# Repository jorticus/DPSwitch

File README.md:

# DPSwitch #

*License: CERN-OHL-S v2*

DPSwitch is a simple KVM-style device that allows you to switch Display Port & USB2.0 between two source devices (eg. a Laptop and a PC):

It is built around the HD3SS215 DP/HDMI mux chip by Texas Instruments, and has a simple flip-flop circuit and two physical buttons to select the input to route to the output. No firmware is required!

I abuse the HD3SS215's HDMI DDC lines to switch USB2.0 signals, and while the datasheet doesn't specify a maximum bandwidth for these lines, it appears to work fine. This avoids the need for a separate mux to switch USB.

## Bill of Materials ##

Qty | Description               | Part Number
----|---------------------------|------------
  1 | DP/HDMI 2:1 Mux 6Gbps     | HD3SS215RTQT
  1 | Dual NAND Gate            | 74LVC2G00DC,125
  1 | 0603 Side look LED (Blue) | KPA-1606QBC-D
  2 | 0603 SMD LED (Green)      | 
  2 | Button (SMD)              | PTS645*
  1 | USB Type-A Conn (TH)      | SS-52100-001
  2 | Micro USB Conn (SMD)      | 609-5379-2-ND 
  2 | Diode                     | BAT54GWJ
  3 | DisplayPort Conn          | MOLEX 47272-0001

Plus various 0603 resistors & capacitors. See schematic.

## Manufacturing ##

Since DP operates in the GHz range, the PCB must be impedance controlled, and utilizes a 4 layer stackup. I used JLCPCB's 4-layer '[JLC7628](https://jlcpcb.com/quote/pcbOrderFaq/PCB%20Stackup)' PCB with a dielectric constant of 4.6, and a black solder mask.

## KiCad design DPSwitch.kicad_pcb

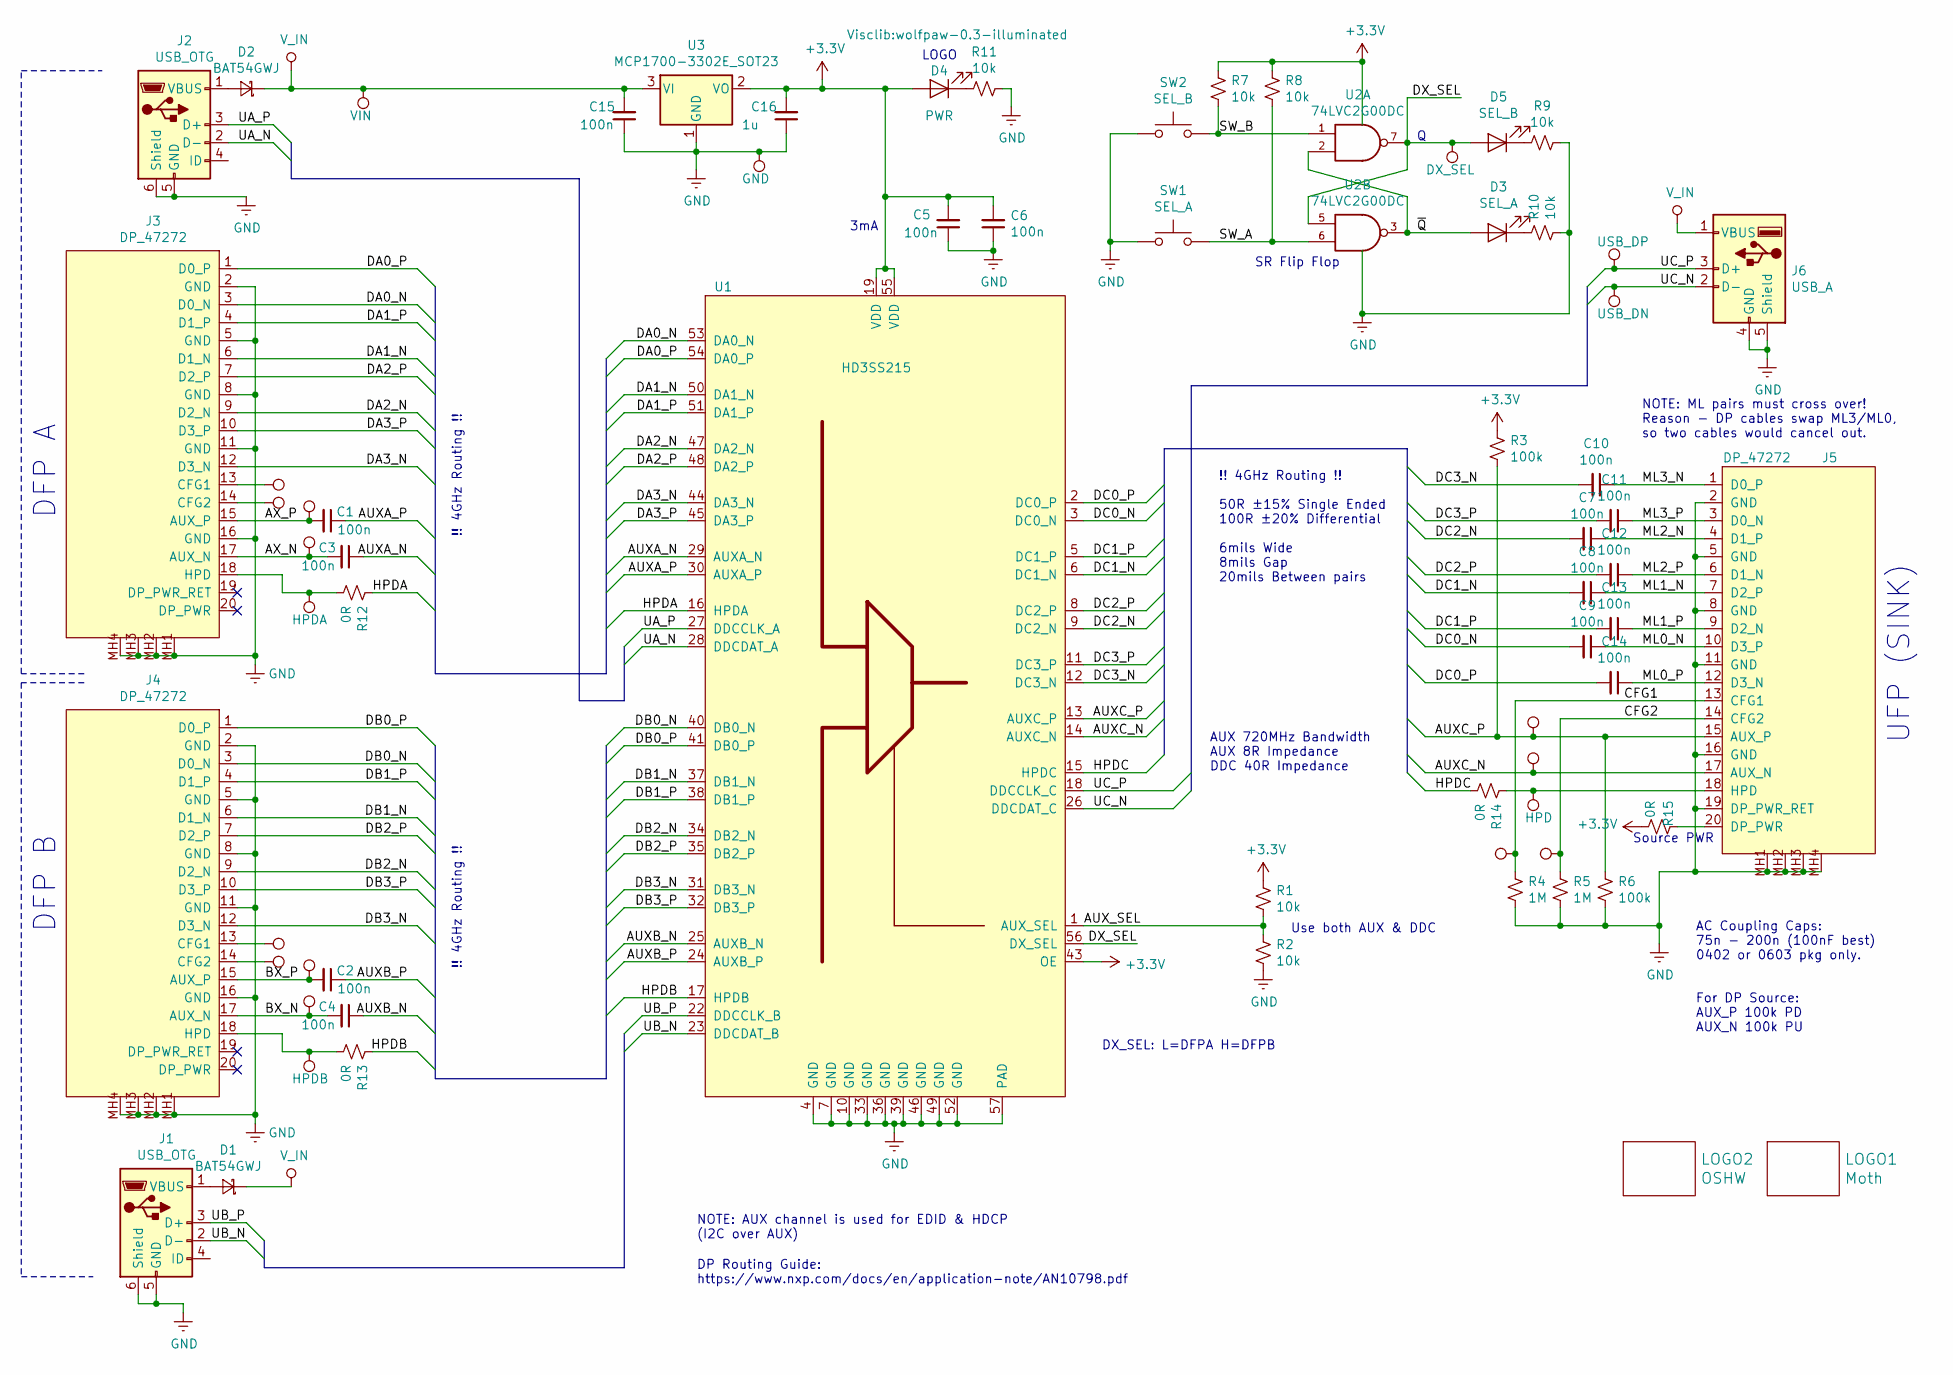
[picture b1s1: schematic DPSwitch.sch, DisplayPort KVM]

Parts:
C1, C2, C3, C4, C5, C6, C7, C8, C9, C10, C11, C12, C13, C14, C15: 100n; C_0603_HandSoldering
C16: 1u; C_0805_HandSoldering
D1, D2: BAT54GWJ; D_SOD-123
D3: SEL_A; LED_0603_HandSoldering
D4: PWR; wolfpaw-0.3-illuminated
D5: SEL_B; LED_0603_HandSoldering
J1, J2: USB_OTG; USB-B-MICRO-SMD
J3, J4, J5: DP_47272; 472720024
J6: USB_A
LOGO1: Moth; moth
LOGO2: OSHW; OSHW-LOGO-M
R1, R2, R7, R8, R9, R10, R11: 10k; R_0603_HandSoldering
R3, R6: 100k; R_0603_HandSoldering
R4, R5: 1M; R_0603_HandSoldering
R12, R13, R14, R15: 0R; R_0603_HandSoldering
SW1: SEL_A; SW_SPST_PTS645
SW2: SEL_B; SW_SPST_PTS645
TP1: CFG1A; TP-1MM
TP2: CFG2A; TP-1MM
TP3: CFG1B; TP-1MM
TP4: CFG2B; TP-1MM
TP5: AUXA_P; TP-1MM
TP6: AUXA_N; TP-1MM
TP7: HPDA; TP-1MM
TP8: AUXB_P; TP-1MM
TP9: AUXB_N; TP-1MM
TP10: HPDB; TP-1MM
TP11: VIN; TP-1MM
TP13: DX_SEL; TP-1MM
TP14: CFG1; TP-1MM
TP15: AUX_P; TP-1MM
TP16: AUX_N; TP-1MM
TP17: HPD; TP-1MM
TP18: CFG2; TP-1MM
TP19: USB_DP; TP-1MM
TP20: USB_DN; TP-1MM
TP21: GND; TP-1MM
U1: HD3SS215; VQFN-56_EP_7.8x7.8_Pitch0.5mm
U2: 74LVC2G00DC; VSSOP-8_2.4x2.1mm_Pitch0.5mm
U3: MCP1700-3302E_SOT23; SOT-23

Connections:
+3V3: C5.2, C6.2, C16.2, D4.2 (A), R1.1, R3.1, R7.1, R8.1, R15.2, U1.19 (VDD), U1.43 (OE), U1.55 (VDD), U2.8 (VCC), U3.2 (VO)
/AUXA_N: C3.1, U1.29 (AUXA_N)
/AUXA_P: C1.1, U1.30 (AUXA_P)
/AUXB_N: C4.1, U1.25 (AUXB_N)
/AUXB_P: C2.1, U1.24 (AUXB_P)
/AUXC_N: J5.17 (AUX_N), TP16.1, U1.14 (AUXC_N)
/AUXC_P: J5.15 (AUX_P), R3.2, R6.1, TP15.1, U1.13 (AUXC_P)
/AUX_SEL: R1.2, R2.1, U1.1 (AUX_SEL)
/AX_N: C3.2, J3.17 (AUX_N), TP6.1
/AX_P: C1.2, J3.15 (AUX_P), TP5.1
/BX_N: C4.2, J4.17 (AUX_N), TP9.1
/BX_P: C2.2, J4.15 (AUX_P), TP8.1
/CFG1: J5.13 (CFG1), R4.1, TP14.1
/CFG2: J5.14 (CFG2), R5.1, TP18.1
/DA0_N: J3.3 (D0_N), U1.53 (DA0_N)
/DA0_P: J3.1 (D0_P), U1.54 (DA0_P)
/DA1_N: J3.6 (D1_N), U1.50 (DA1_N)
/DA1_P: J3.4 (D1_P), U1.51 (DA1_P)
/DA2_N: J3.9 (D2_N), U1.47 (DA2_N)
/DA2_P: J3.7 (D2_P), U1.48 (DA2_P)
/DA3_N: J3.12 (D3_N), U1.44 (DA3_N)
/DA3_P: J3.10 (D3_P), U1.45 (DA3_P)
/DB0_N: J4.3 (D0_N), U1.40 (DB0_N)
/DB0_P: J4.1 (D0_P), U1.41 (DB0_P)
/DB1_N: J4.6 (D1_N), U1.37 (DB1_N)
/DB1_P: J4.4 (D1_P), U1.38 (DB1_P)
/DB2_N: J4.9 (D2_N), U1.34 (DB2_N)
/DB2_P: J4.7 (D2_P), U1.35 (DB2_P)
/DB3_N: J4.12 (D3_N), U1.31 (DB3_N)
/DB3_P: J4.10 (D3_P), U1.32 (DB3_P)
/DC0_N: C9.2, U1.3 (DC0_N)
/DC0_P: C14.2, U1.2 (DC0_P)
/DC1_N: C8.2, U1.6 (DC1_N)
/DC1_P: C13.2, U1.5 (DC1_P)
/DC2_N: C7.2, U1.9 (DC2_N)
/DC2_P: C12.2, U1.8 (DC2_P)
/DC3_N: C10.2, U1.12 (DC3_N)
/DC3_P: C11.2, U1.11 (DC3_P)
/DX_SEL: D5.2 (A), TP13.1, U1.56 (DX_SEL), U2.5, U2.7
/HPDA: R12.1, U1.16 (HPDA)
/HPDB: R13.1, U1.17 (HPDB)
/HPDC: R14.2, U1.15 (HPDC)
/ML0_N: C9.1, J5.10 (D3_P)
/ML0_P: C14.1, J5.12 (D3_N)
/ML1_N: C8.1, J5.7 (D2_P)
/ML1_P: C13.1, J5.9 (D2_N)
/ML2_N: C7.1, J5.4 (D1_P)
/ML2_P: C12.1, J5.6 (D1_N)
/ML3_N: C10.1, J5.1 (D0_P)
/ML3_P: C11.1, J5.3 (D0_N)
/SW_A: R8.2, SW1.2, U2.6
/SW_B: R7.2, SW2.2, U2.1
/UA_N: J2.2 (D-), U1.28 (DDCDAT_A)
/UA_P: J2.3 (D+), U1.27 (DDCCLK_A)
/UB_N: J1.2 (D-), U1.23 (DDCDAT_B)
/UB_P: J1.3 (D+), U1.22 (DDCCLK_B)
/UC_N: J6.2 (D-), TP20.1, U1.26 (DDCDAT_C)
/UC_P: J6.3 (D+), TP19.1, U1.18 (DDCCLK_C)
/~Q: D3.2 (A), U2.2, U2.3
GND: C5.1, C6.1, C15.1, C16.1, J1.5 (GND), J1.6 (Shield), J2.5 (GND), J2.6 (Shield), J3.2 (GND), J3.5 (GND), J3.8 (GND), J3.11 (GND), J3.16 (GND), J3.MH1, J3.MH2, J3.MH3, J3.MH4, J4.2 (GND), J4.5 (GND), J4.8 (GND), J4.11 (GND), J4.16 (GND), J4.MH1, J4.MH2, J4.MH3, J4.MH4, J5.2 (GND), J5.5 (GND), J5.8 (GND), J5.11 (GND), J5.16 (GND), J5.19 (DP_PWR_RET), J5.MH1, J5.MH2, J5.MH3, J5.MH4, J6.4 (GND), J6.5 (Shield), R2.2, R4.2, R5.2, R6.2, R9.1, R10.2, R11.1, SW1.1, SW2.1, TP21.1, U1.4 (GND), U1.7 (GND), U1.10 (GND), U1.33 (GND), U1.36 (GND), U1.39 (GND), U1.46 (GND), U1.49 (GND), U1.52 (GND), U1.57 (PAD), U2.4 (GND), U3.1 (GND)
unnamed: D1.2 (A), J1.1 (VBUS)
unnamed: D2.2 (A), J2.1 (VBUS)
unnamed: D3.1 (K), R10.1
unnamed: D4.1 (K), R11.2
unnamed: D5.1 (K), R9.2
unnamed: J3.13 (CFG1), TP1.1
unnamed: J3.14 (CFG2), TP2.1
unnamed: J3.18 (HPD), R12.2, TP7.1
unnamed: J4.13 (CFG1), TP3.1
unnamed: J4.14 (CFG2), TP4.1
unnamed: J4.18 (HPD), R13.2, TP10.1
unnamed: J5.18 (HPD), R14.1, TP17.1
unnamed: J5.20 (DP_PWR), R15.1
VDD: C15.2, D1.1 (K), D2.1 (K), J6.1 (VBUS), TP11.1, U3.3 (VI)

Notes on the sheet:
UFP (SINK)
DFP A
DFP B
For DP Source: AUX_P 100k PD AUX_N 100k PU
DX_SEL: L=DFPA H=DFPB
AUX 720MHz Bandwidth AUX 8R Impedance DDC 40R Impedance
NOTE: AUX channel is used for EDID & HDCP (I2C over AUX)
AC Coupling Caps: 75n - 200n (100nF best) 0402 or 0603 pkg only.
Use both AUX & DDC
!! 4GHz Routing !!
NOTE: ML pairs must cross over! Reason - DP cables swap ML3/ML0, so two cables would cancel out.
Source PWR
3mA
!! 4GHz Routing !! 50R ±15% Single Ended 100R ±20% Differential 6mils Wide 8mils Gap 20mils Between pairs
DP Routing Guide: https://www.nxp.com/docs/en/application-note/AN10798.pdf
LOGO
SR Flip Flop

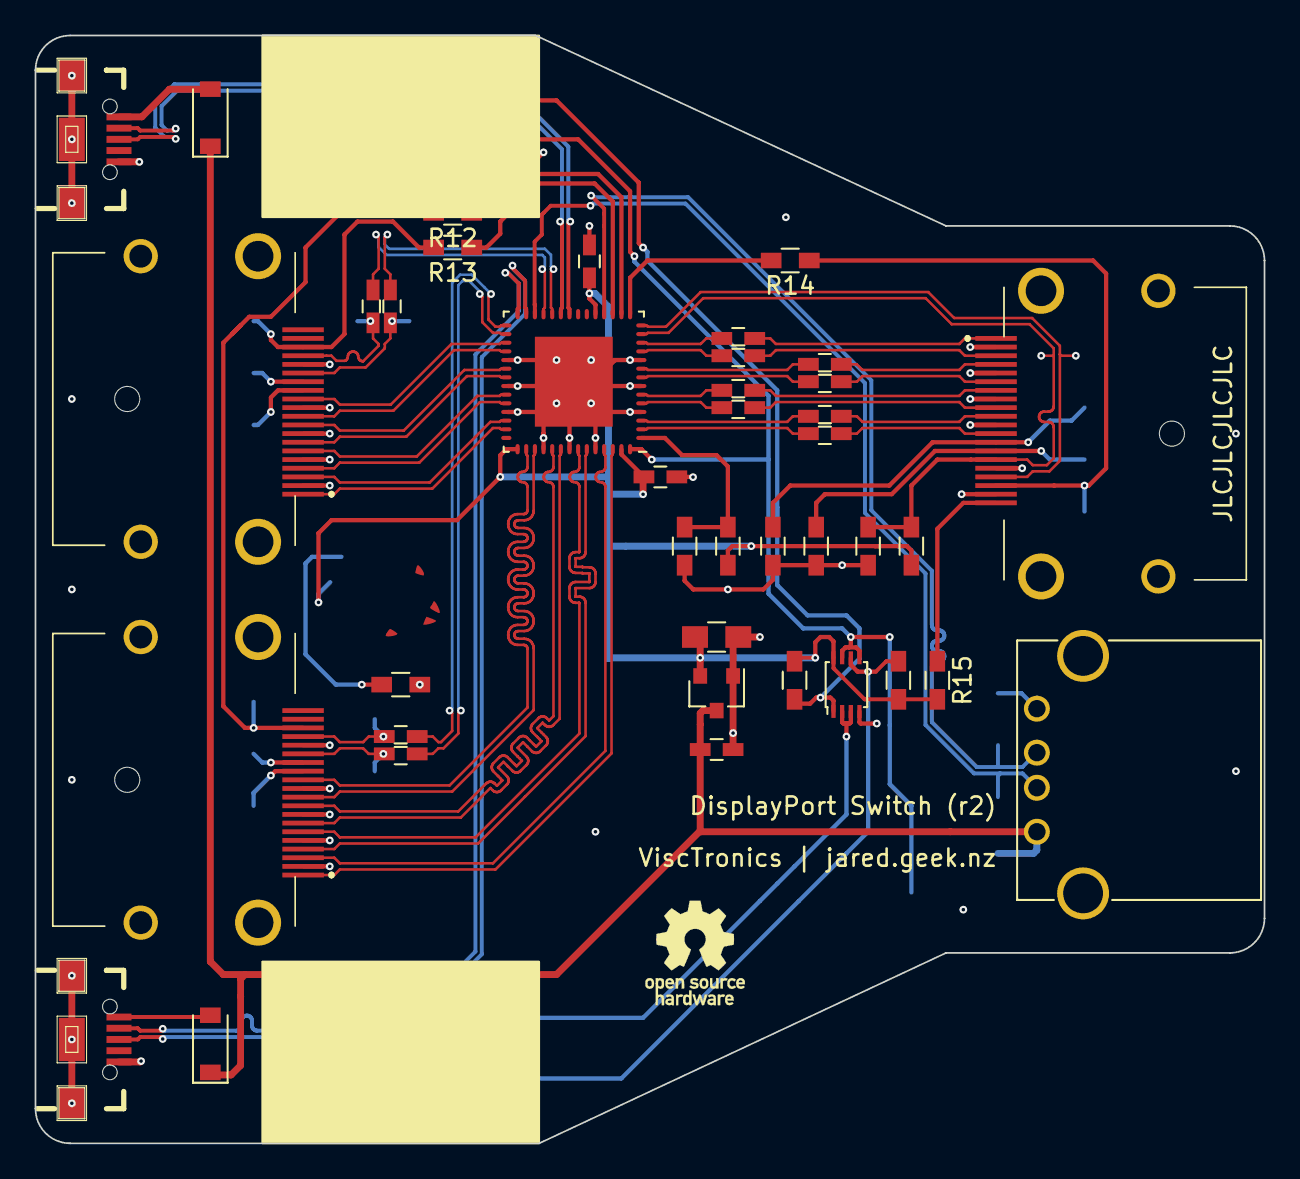
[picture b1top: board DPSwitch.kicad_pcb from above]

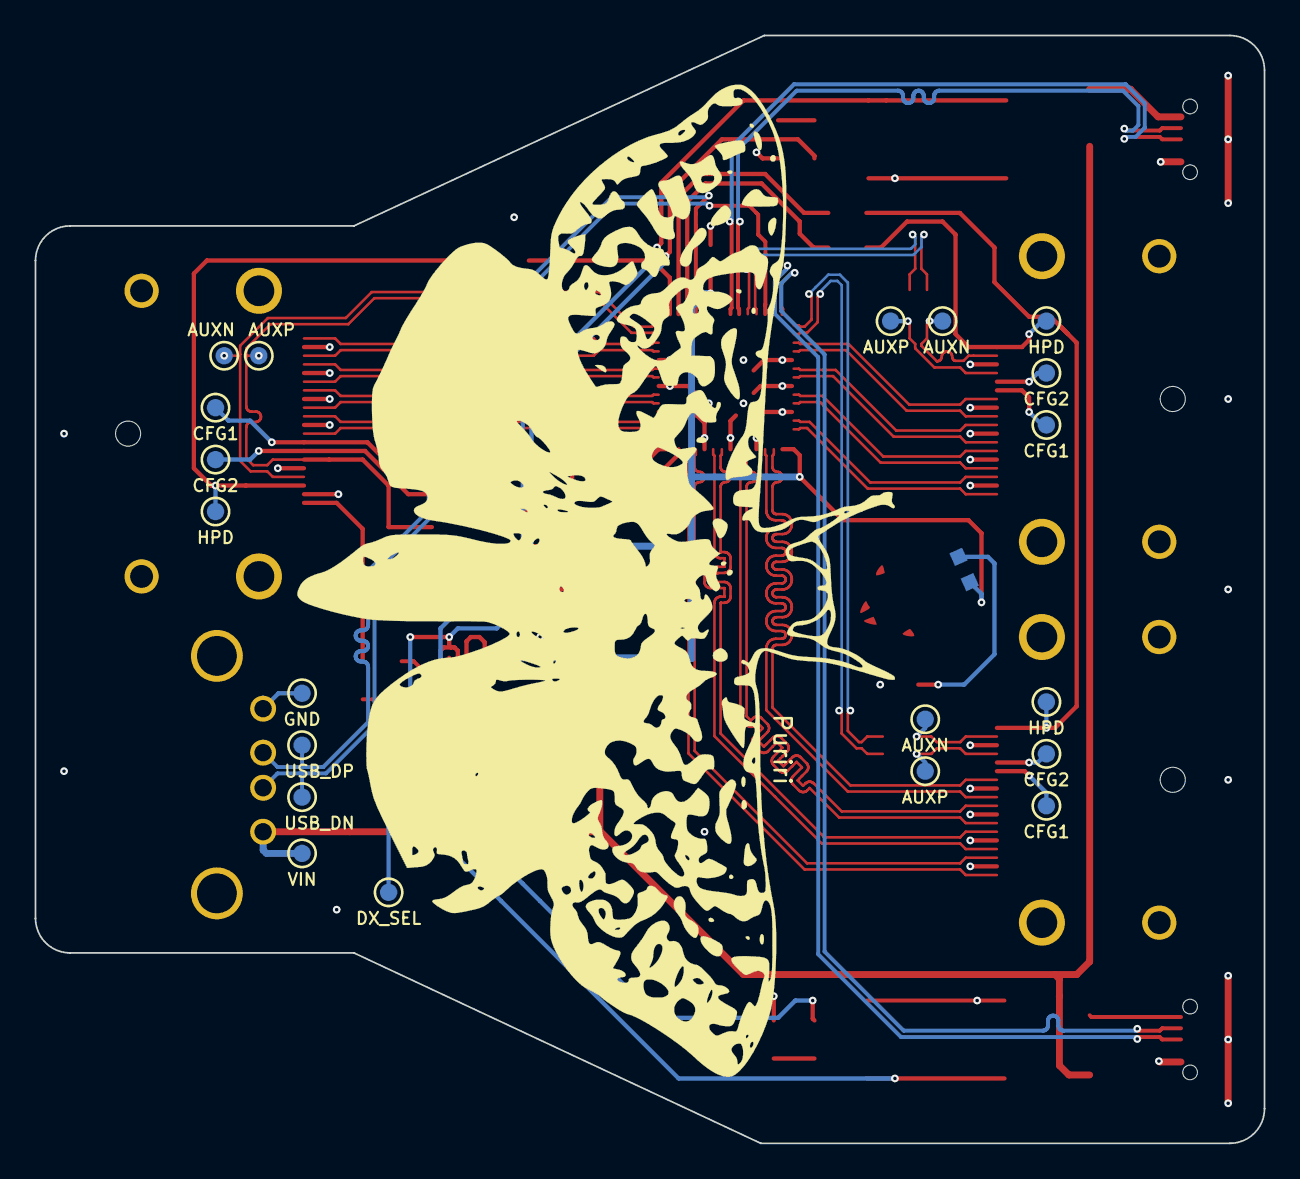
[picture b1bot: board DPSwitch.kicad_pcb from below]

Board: 4 copper layers, 71.0 x 64.0 mm, 69 parts (21 on the bottom side), 74 nets.

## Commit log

2021-01-19 Add README/License
2021-01-19 Final gerbers rev1.2
2021-01-19 Added moth
2021-01-19 Rev1 for manufacture
2021-01-19 r2 - Swap USB A/B inputs, fix inverted flip-flop logic
2021-01-19 Tidy up fabrication layer
2021-01-19 Add testpads, 0R resistors to allow reconfiguration, and OSHW logo
2021-01-19 Rev2 for manufacture
